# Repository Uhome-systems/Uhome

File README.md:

- 👋 Hi, I’m @Uhome-Systems
- 🌐 Our website is https://uhome.systems/
- 👀 I’m interested in smart home systems
- 📫 How to reach me info@uhome.systems
- 💬 Join our Discord here: https://discord.gg/JBZaJAvD

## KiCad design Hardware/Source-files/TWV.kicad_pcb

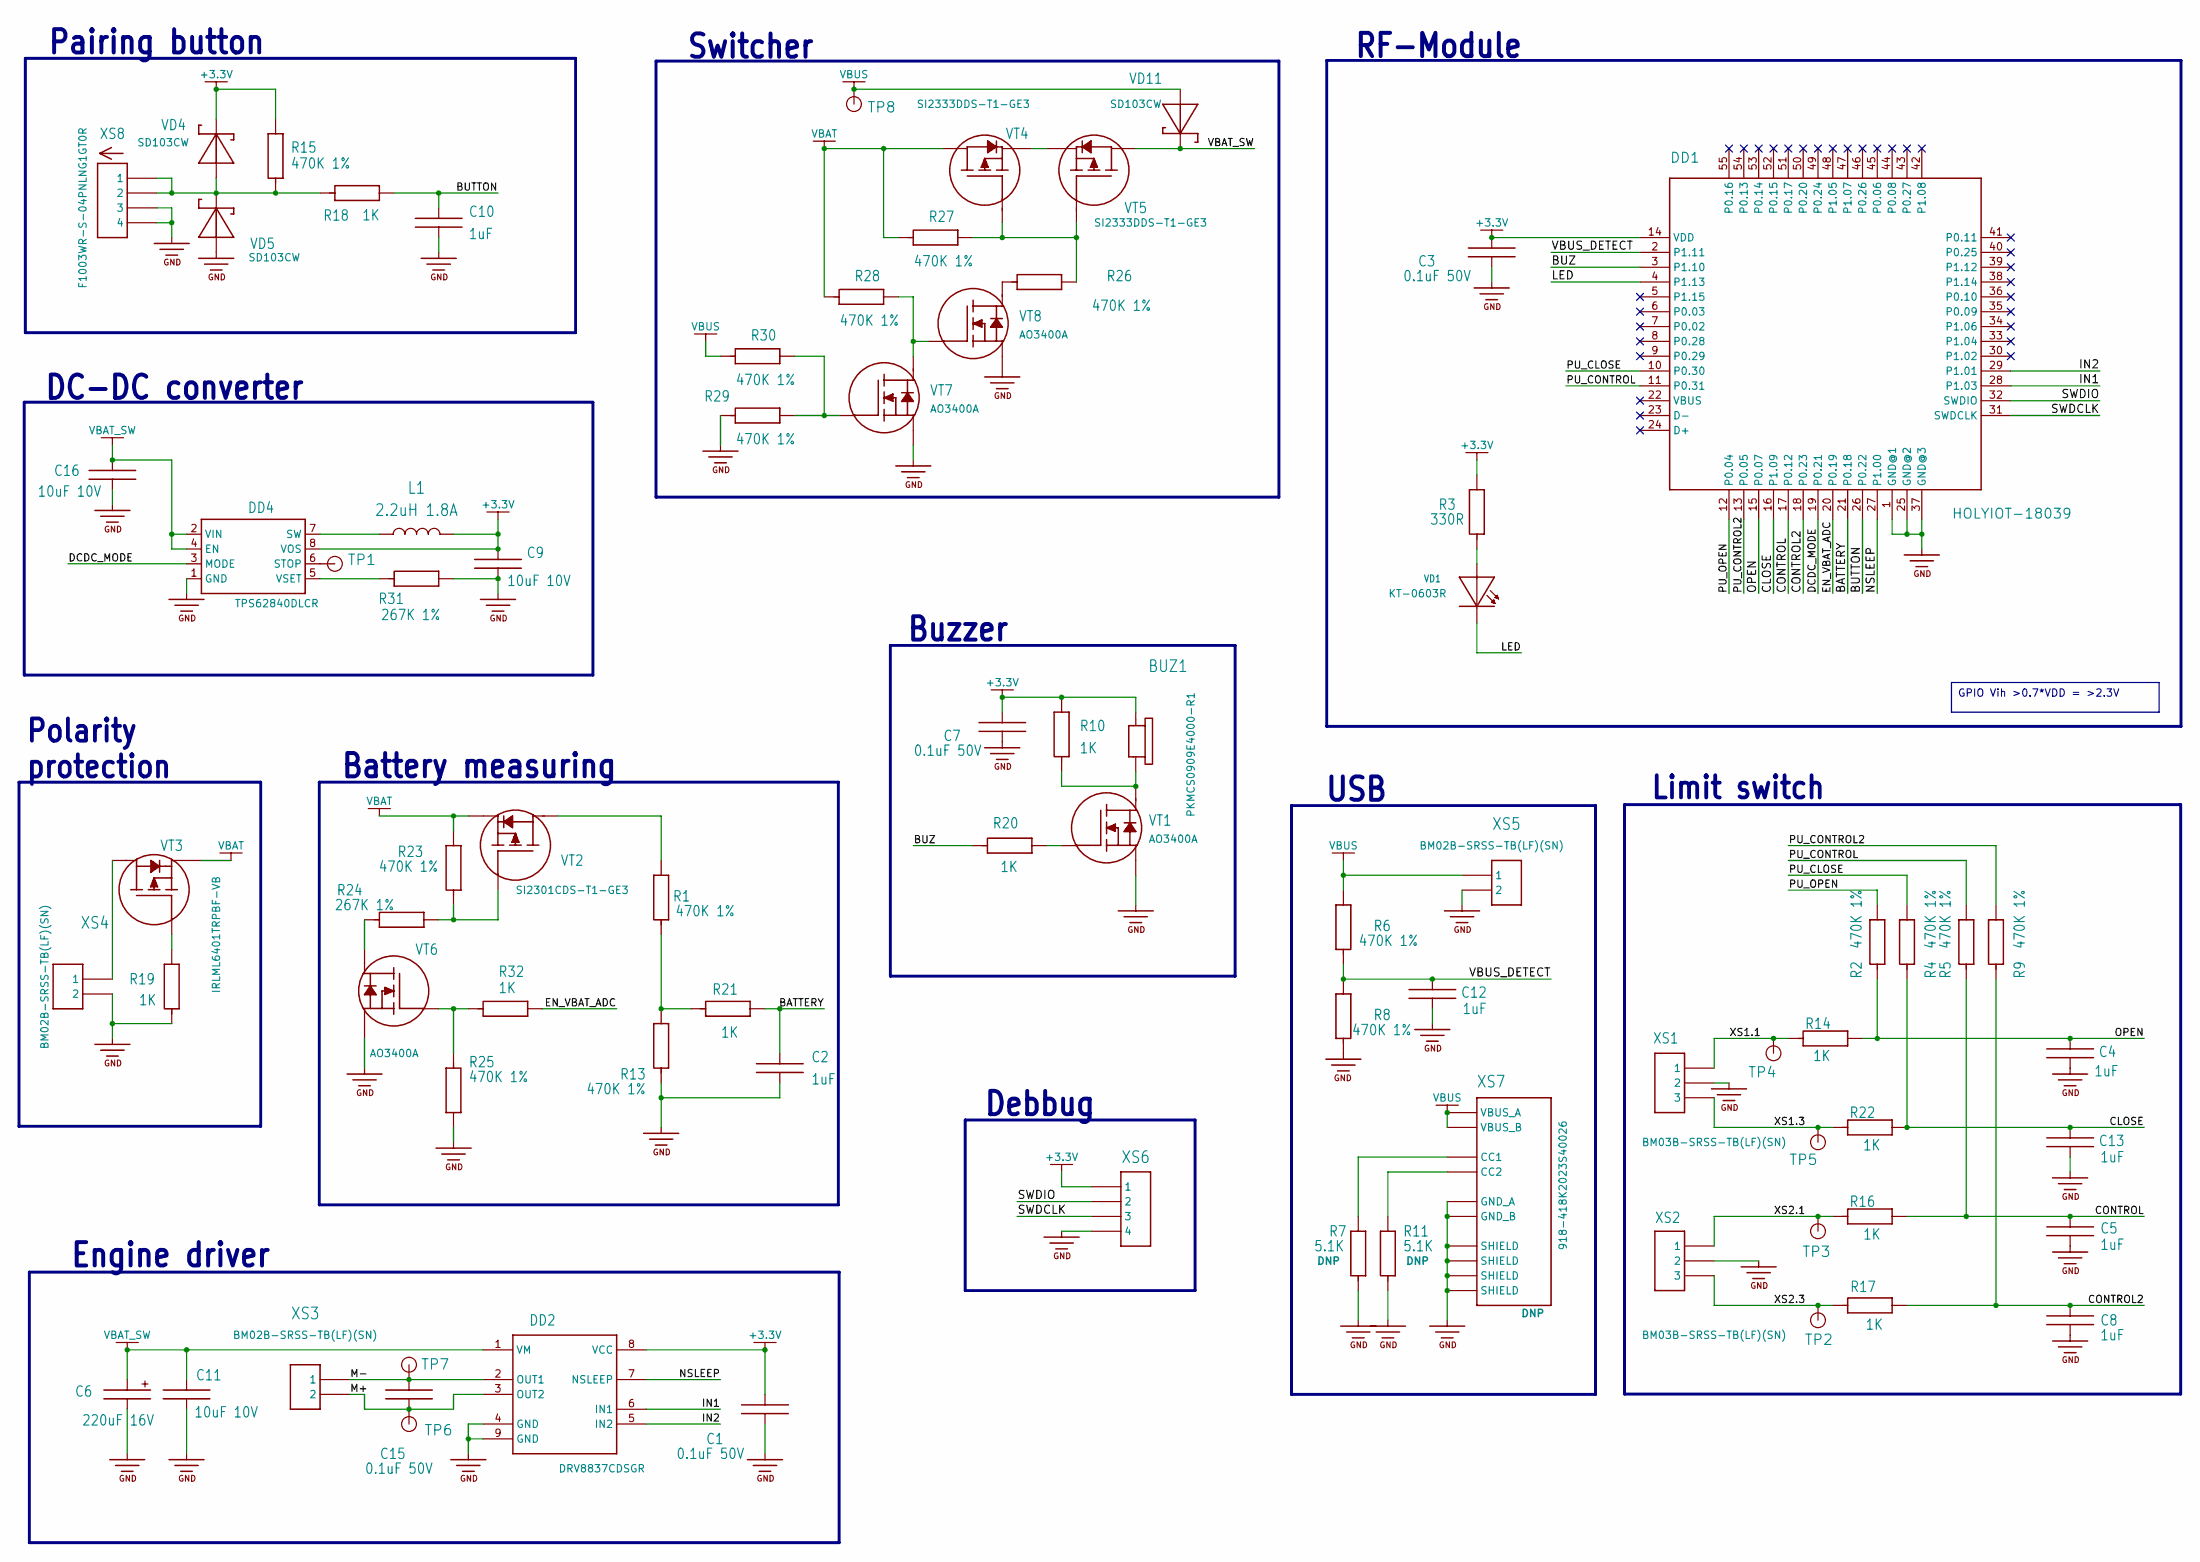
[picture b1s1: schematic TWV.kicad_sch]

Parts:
BUZ1: PKMCS0909E4000-R1; Manufacturer PN PKMCS0909E4000-R1; JLCPCB PN C910763
C1, C3, C7, C15: 0.1uF 50V; C_0603_1608Metric; Manufacturer PN CC0603KRX7R9BB104; JLCPCB PN C14663
C2, C4, C5, C8, C10, C12, C13: 1uF; C_0603_1608Metric; Manufacturer PN CL10A105KB8NNNC; JLCPCB PN C15849
C6: 220uF 16V; CP_Elec_6.3x7.7; Manufacturer PN VT220UF16V167RV0088; JLCPCB PN C5246575
C9, C11, C16: 10uF 10V; C_0603_1608Metric; Manufacturer PN CL10A106KP8NNNC; JLCPCB PN C19702
DD1: HOLYIOT-18039
DD2: WSON-8; Manufacturer PN DRV8837CDSGR; JLCPCB PN C191000
DD4: VSON-8; Manufacturer PN TPS62840DLCR; JLCPCB PN C2071859
L1: 2.2uH 1.8A; L_0805_2012Metric; Manufacturer PN DFE201612E-2R2M=P2; JLCPCB PN C337893
R1, R2, R4, R5, R6, R8, R9, R13, R15, R23, R25, R26, R27, R28, R29, R30: 470K 1%; R_0603_1608Metric; Manufacturer PN 0603WAF4703T5E; JLCPCB PN C23178
R3: 330R; R_0603_1608Metric; Manufacturer PN 0603WAF3300T5E; JLCPCB PN C23138
R7, R11: 5.1K; R_0603_1608Metric; Manufacturer PN 0603WAF5101T5E; JLCPCB PN C23186
R10, R14, R16, R17, R18, R19, R20, R21, R22, R32: 1K; R_0603_1608Metric; Manufacturer PN 0603WAF1001T5E; JLCPCB PN C21190
R24, R31: 267K 1%; R_0603_1608Metric; Manufacturer PN 0603WAF2673T5E; JLCPCB PN C22963
TP1, TP2, TP3, TP4, TP5, TP6, TP7, TP8: TEST_POINT_2MM
VD1: LED_0603; Manufacturer PN KT-0603R; JLCPCB PN C2286
VD4, VD5: SD103CW-AQ; D_SOD-123F; Manufacturer PN SD103CW; JLCPCB PN C21572
VD11: D_SOD-123F; Manufacturer PN SD103CW; JLCPCB PN C21572
VT1, VT6, VT7, VT8: Q_SOT-23; Manufacturer PN AO3400A; JLCPCB PN C20917
VT2: P-type; Q_SOT-23; Manufacturer PN SI2301CDS-T1-GE3; JLCPCB PN C10487
VT3: Q_SOT-23; Manufacturer PN IRLML6401TRPBF-VB; JLCPCB PN C558179
VT4, VT5: Q_SOT-23; Manufacturer PN SI2333DDS-T1-GE3; JLCPCB PN C183004
XS1, XS2: BM03B-SRSS-TB; Manufacturer PN BM03B-SRSS-TB(LF)(SN); JLCPCB PN C160389
XS3, XS5: BM02B-SRSS-TB; Manufacturer PN BM02B-SRSS-TB(LF)(SN); JLCPCB PN C160388
XS4: BM02B-SRSS-TB; Manufacturer PN BM02B-SRSS-TB(LF)(SN); JLCPCB PN C160388
XS6: TH1X4-2.54MM
XS7: 918-418K2023S40026; Manufacturer PN 918-418K2023S40026; JLCPCB PN C2763104
XS8: F1003WR-S-04PNLNG1GT0R; Manufacturer PN F1003WR-S-04PNLNG1GT0R; JLCPCB PN C247801

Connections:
+3.3V: BUZ1.1 (+), C1.1, C3.1, C7.1, C9.1, DD1.14 (VDD), DD2.8 (VCC), DD4.8 (VOS), L1.2, R3.2, R10.2, R15.2, VD4.C, XS6.1
/BATTERY: C2.1, DD1.21 (P0.18), R21.2
/BUTTON: C10.1, DD1.26 (P0.22), R18.2
/BUZ: DD1.3 (P1.10), R20.1
/CLOSE: C13.1, DD1.16 (P1.09), R4.1, R22.2
/CONTROL: C5.1, DD1.17 (P0.12), R5.1, R16.2
/CONTROL2: C8.1, DD1.18 (P0.23), R9.1, R17.2
/DCDC_MODE: DD1.19 (P0.21), DD4.3 (MODE)
/EN_VBAT_ADC: DD1.20 (P0.19), R32.2
/IN1: DD1.28 (P1.03), DD2.6 (IN1)
/IN2: DD1.29 (P1.01), DD2.5 (IN2)
/LED: DD1.4 (P1.13), VD1.1 (C)
/M+: C15.2, DD2.3 (OUT2), TP6.1, XS3.2
/M-: C15.1, DD2.2 (OUT1), TP7.1, XS3.1
/NSLEEP: DD1.27 (P1.00), DD2.7 (NSLEEP)
/OPEN: C4.1, DD1.15 (P0.07), R2.1, R14.2
/PU_CLOSE: DD1.10 (P0.30), R4.2
/PU_CONTROL: DD1.11 (P0.31), R5.2
/PU_CONTROL2: DD1.13 (P0.05), R9.2
/PU_OPEN: DD1.12 (P0.04), R2.2
/SWDCLK: DD1.31 (SWDCLK), XS6.3
/SWDIO: DD1.32 (SWDIO), XS6.2
/VBUS_DETECT: C12.1, DD1.2 (P1.11), R6.1, R8.2
/XS1.1: R14.1, TP4.1, XS1.1
/XS1.3: R22.1, TP5.1, XS1.3
/XS2.1: R16.1, TP3.1, XS2.1
/XS2.3: R17.1, TP2.1, XS2.3
GND: C1.2, C2.2, C3.2, C4.2, C5.2, C6.2 (-), C7.2, C8.2, C9.2, C10.2, C11.2, C12.2, C13.2, C16.2, DD1.1 (GND@1), DD1.25 (GND@2), DD1.37 (GND@3), DD2.4 (GND), DD2.9 (GND), DD4.1 (GND), R7.1, R8.1, R11.1, R13.1, R19.1, R25.2, R29.1, R31.2, VD5.A, VT1.2 (S), VT6.2 (S), VT7.2 (S), VT8.2 (S), XS1.2, XS2.2, XS4.2, XS5.2, XS6.4, XS7.A12 (GND_A), XS7.B12 (GND_B), XS7.SH1 (SHIELD), XS7.SH2 (SHIELD), XS7.SH3 (SHIELD), XS7.SH4 (SHIELD), XS8.3, XS8.4
unnamed: BUZ1.2 (-), R10.1, VT1.3 (D)
unnamed: DD4.6 (STOP), TP1.1
unnamed: DD4.7 (SW), L1.1
unnamed: DD4.5 (VSET), R31.1
unnamed: R1.1, R13.2, R21.1
unnamed: R15.1, R18.1, VD4.A, VD5.C, XS8.1, XS8.2
unnamed: R3.1, VD1.2 (A)
unnamed: R20.2, VT1.1 (G)
unnamed: R1.2, VT2.3 (D)
unnamed: R23.1, R24.2, VT2.1 (G)
unnamed: VT3.3 (D), XS4.1
unnamed: R19.2, VT3.1 (G)
unnamed: R26.2, R27.2, VT4.1 (G), VT5.1 (G)
unnamed: VT4.2 (S), VT5.2 (S)
unnamed: R24.1, VT6.3 (D)
unnamed: R25.1, R32.1, VT6.1 (G)
unnamed: R28.2, VT7.3 (D), VT8.1 (G)
unnamed: R29.2, R30.2, VT7.1 (G)
unnamed: R26.1, VT8.3 (D)
unnamed: R7.2, XS7.A5 (CC1)
unnamed: R11.2, XS7.B5 (CC2)
VBAT: R23.2, R27.1, R28.1, VT2.2 (S), VT3.2 (S), VT4.3 (D)
VBAT_SW: C6.1 (+), C11.1, C16.1, DD2.1 (VM), DD4.2 (VIN), DD4.4 (EN), VD11.C, VT5.3 (D)
VBUS: R6.2, R30.1, TP8.1, VD11.A, XS5.1, XS7.A9 (VBUS_A), XS7.B9 (VBUS_B)

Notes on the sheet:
GPIO Vih >0.7*VDD = >2.3V
Battery measuring
Pairing button
Debbug
Switcher
Engine driver
USB
Limit switch
Buzzer
Polarity protection
RF-Module
DC-DC converter

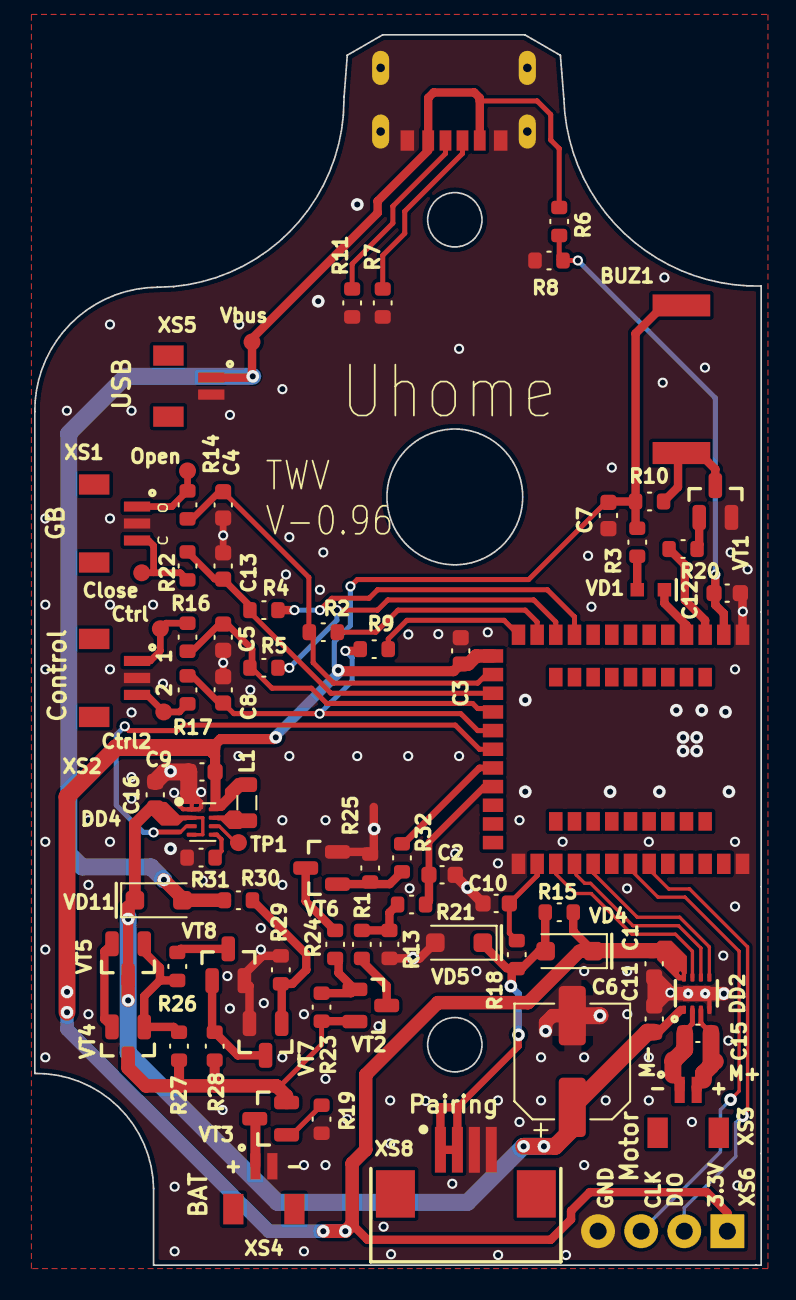
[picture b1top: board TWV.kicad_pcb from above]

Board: 2 copper layers, 42.8 x 72.5 mm, 79 parts (0 on the bottom side), 52 nets.

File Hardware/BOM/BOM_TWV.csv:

"Value","Manufacturer PN","Designator","Footprint","JLCPCB Part#","Qty"
"TEST_POINT_2MM","","TP1,TP2,TP3,TP4,TP5,TP6,TP7,TP8","TWV:TEST_POINT_2MM","","8"
"~","AO3400A","VT1,VT6,VT7,VT8","TWV:Q_SOT-23","C20917","4"
"~","F1003WR-S-04PNLNG1GT0R","XS8","TWV:F1003WR-S-04PNLNG1GT0R","C247801","1"
"~","KT-0603R","VD1","TWV:LED_0603","C2286","1"
"-- mixed values --","SD103CW","VD4,VD5,VD11","TWV:D_SOD-123F","C21572","3"
"BM03B-SRSS-TB","BM03B-SRSS-TB(LF)(SN)","XS1,XS2","TWV:BM03B-SRSS-TB","C160389","2"
"-- mixed values --","BM02B-SRSS-TB(LF)(SN)","XS3,XS4,XS5","TWV:BM02B-SRSS-TB","C160388","3"
"220uF 16V","VT220UF16V167RV0088","C6","TWV:CP_Elec_6.3x7.7","C5246575","1"
"2.2uH 1.8A","DFE201612E-2R2M=P2","L1","TWV:L_0805_2012Metric","C337893","1"
"~","PKMCS0909E4000-R1","BUZ1","TWV:PKMCS0909E4000-R1","C910763","1"
"1uF","CL10A105KB8NNNC","C2,C4,C5,C8,C10,C12,C13","TWV:C_0603_1608Metric","C15849","7"
"10uF 10V","CL10A106KP8NNNC","C9,C11,C16","TWV:C_0603_1608Metric","C19702","3"
"~","DRV8837CDSGR","DD2","TWV:WSON-8","C191000","1"
"~","TPS62840DLCR","DD4","TWV:VSON-8","C2071859","1"
"470K 1%","0603WAF4703T5E","R1,R2,R4,R5,R6,R8,R9,R13,R15,R23,R25,R26,R27,R28,R29,R30","TWV:R_0603_1608Metric","C23178","16"
"330R","0603WAF3300T5E","R3","TWV:R_0603_1608Metric"," C23138","1"
"1K","0603WAF1001T5E","R10,R14,R16,R17,R18,R19,R20,R21,R22,R32","TWV:R_0603_1608Metric","C21190","10"
"267K 1%","0603WAF2673T5E","R24,R31","TWV:R_0603_1608Metric","C22963","2"
"~","IRLML6401TRPBF-VB","VT3","TWV:Q_SOT-23","C558179","1"
"P-type","SI2301CDS-T1-GE3","VT2","TWV:Q_SOT-23","C10487","1"
"~","SI2333DDS-T1-GE3","VT4,VT5","TWV:Q_SOT-23","C183004","2"
"0.1uF 50V","CC0603KRX7R9BB104","C1,C3,C7,C15","TWV:C_0603_1608Metric","C14663","4"

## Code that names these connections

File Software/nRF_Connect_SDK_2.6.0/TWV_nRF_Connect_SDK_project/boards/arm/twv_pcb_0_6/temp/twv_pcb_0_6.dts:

// Copyright (c) 2023 Nordic Semiconductor ASA
// SPDX-License-Identifier: Apache-2.0

/dts-v1/;
#include <nordic/nrf52840_qiaa.dtsi>
#include "twv_pcb_0_6-pinctrl.dtsi"

/ {
	model = "TWV_PCB_0_6";
	compatible = "uhome,twv-pcb-0-6";

	chosen {
		zephyr,console = &uart0;
		zephyr,shell-uart = &uart0;
		zephyr,uart-mcumgr = &uart0;
		zephyr,bt-mon-uart = &uart0;
		zephyr,bt-c2h-uart = &uart0;
		zephyr,sram = &sram0;
		zephyr,flash = &flash0;
		zephyr,code-partition = &slot0_partition;
		zephyr,ieee802154 = &ieee802154;
	};

	buttons {
		compatible = "gpio-keys";
		pairing {
			gpios = <&gpio1 2 (GPIO_ACTIVE_LOW)>;
			label = "Pairing button";
		};

		open {
			gpios = <&gpio1 13 (GPIO_ACTIVE_LOW)>;
			label = "GB Open limmit switch";
		};

		close {
			gpios = <&gpio1 15 (GPIO_ACTIVE_LOW)>;
			label = "GB Close limmit switch";
		};

		contro_1 {
			gpios = <&gpio0 3 (GPIO_ACTIVE_LOW)>;
			label = "Control limmit switch 1";
		};

		control_2 {
			gpios = <&gpio0 5 (GPIO_ACTIVE_LOW)>;
			label = "Control limmit switch 2";
		};
	};

	led_indication {
		compatible = "gpio-leds";
		pairing_led {
			gpios = <&gpio1 4 (GPIO_ACTIVE_LOW)>;
		};

		error_led {
			gpios = <&gpio1 6 (GPIO_ACTIVE_LOW)>;
		};

		open_status_led {
			gpios = <&gpio0 18 (GPIO_ACTIVE_LOW)>;
		};

		close_status_led {
			gpios = <&gpio0 19 0>;
		};
	};
};

&flash0 {

	partitions {
		compatible = "fixed-partitions";
		#address-cells = <1>;
		#size-cells = <1>;

		boot_partition: partition@0 {
			label = "mcuboot";
			reg = <0x00000000 0x0000C000>;
		};
		slot0_partition: partition@c000 {
			label = "image-0";
			reg = <0x0000C000 0x00076000>;
		};
		slot1_partition: partition@82000 {
			label = "image-1";
			reg = <0x00082000 0x00076000>;
		};

		/*
		 * The flash starting at 0x000f8000 and ending at
		 * 0x000fffff is reserved for use by the application.
		 */

		/*
		 * Storage partition will be used by FCB/LittleFS/NVS
		 * if enabled.
		 */
		storage_partition: partition@f8000 {
			label = "storage";
			reg = <0x000f8000 0x00008000>;
		};
	};
};

&adc {
    status = "okay";
};

&gpio0 {
    status = "okay";
};

&gpio1 {
    status = "okay";
};

&gpiote {
    status = "okay";
};

&uart1 {
	current-speed = <115200>;
	pinctrl-0 = <&uart1_default>;
	pinctrl-1 = <&uart1_sleep>;
	pinctrl-names = "default", "sleep";
};

&uart0 {
	compatible = "nordic,nrf-uarte";
	status = "okay";
	current-speed = <115200>;
	pinctrl-0 = <&uart0_default>;
	pinctrl-1 = <&uart0_sleep>;
	pinctrl-names = "default", "sleep";
};

&systick {
    status = "okay";
};

&timer4 {
    status = "okay";
};

&timer3 {
    status = "okay";
};

&timer2 {
    status = "okay";
};

&timer1 {
    status = "okay";
};

&timer0 {
    status = "okay";
};

&rtc0 {
    status = "okay";
};

&rtc1 {
    status = "okay";
};

&rtc2 {
    status = "okay";
};

&i2c0 {
	compatible = "nordic,nrf-twi";
	status = "okay";
	pinctrl-0 = <&i2c0_default>;
	pinctrl-1 = <&i2c0_sleep>;
	pinctrl-names = "default", "sleep";
};

&i2c1 {
	compatible = "nordic,nrf-twi";
	/* Cannot be used together with spi1. */
	/* status = "okay"; */
	pinctrl-0 = <&i2c1_default>;
	pinctrl-1 = <&i2c1_sleep>;
	pinctrl-names = "default", "sleep";
};

&pwm0 {
	status = "okay";
	pinctrl-0 = <&pwm0_default>;
	pinctrl-1 = <&pwm0_sleep>;
	pinctrl-names = "default", "sleep";
};

&spi0 {
	compatible = "nordic,nrf-spi";
	/* Cannot be used together with i2c0. */
	/* status = "okay"; */
	pinctrl-0 = <&spi0_default>;
	pinctrl-1 = <&spi0_sleep>;
	pinctrl-names = "default", "sleep";
};

&spi1 {
	compatible = "nordic,nrf-spi";
	status = "okay";
	pinctrl-0 = <&spi1_default>;
	pinctrl-1 = <&spi1_sleep>;
	pinctrl-names = "default", "sleep";
};

&spi2 {
	compatible = "nordic,nrf-spi";
	status = "disabled";
	pinctrl-0 = <&spi2_default>;
	pinctrl-1 = <&spi2_sleep>;
	pinctrl-names = "default", "sleep";
};

&qspi {
	status = "okay";
	pinctrl-0 = <&qspi_default>;
	pinctrl-1 = <&qspi_sleep>;
	pinctrl-names = "default", "sleep";
	mx25r64: mx25r6435f@0 {
		compatible = "nordic,qspi-nor";
		reg = <0>;
		/* MX25R64 supports only pp and pp4io */
		writeoc = "pp4io";
		/* MX25R64 supports all readoc options */
		readoc = "read4io";
		sck-frequency = <8000000>;
		jedec-id = [c2 28 17];
		sfdp-bfp = [
			e5 20 f1 ff  ff ff ff 03  44 eb 08 6b  08 3b 04 bb
			ee ff ff ff  ff ff 00 ff  ff ff 00 ff  0c 20 0f 52
			10 d8 00 ff  23 72 f5 00  82 ed 04 cc  44 83 68 44
			30 b0 30 b0  f7 c4 d5 5c  00 be 29 ff  f0 d0 ff ff
		];
		size = <67108864>;
		has-dpd;
		t-enter-dpd = <10000>;
		t-exit-dpd = <35000>;
	};
};

&ieee802154 {
	status = "okay";
};

zephyr_udc0: &usbd {
	compatible = "nordic,nrf-usbd";
	status = "okay";
};

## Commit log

2023-11-08 Add files via upload
    Initial commit
2023-11-08 Software initial commit
2023-11-09 Schematic update
2023-11-10 Hardware source files
2023-11-13 Add parts in stl format
2024-01-16 Testing bug fixes
2024-01-18 Version number fix
2024-01-18 remove old FOTA pack
2024-01-24 Stable PCB version
2024-04-14 update PCB to V0.96
    PCB development moved from Eagle to KiCAD.
2024-04-14 Firmware version update to V2.24
    Firmware development moved to nRF Connect SDK 2.6.0
